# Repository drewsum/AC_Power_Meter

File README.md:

# AC_Power_Meter
ELEN3035 Final Project

AC Power Meter centered around an 8 bit PIC microcontroller

Built with KiCad 5.0.1 (with custom library), MPLAB X 5.05, and XC8 C compiler 1.45

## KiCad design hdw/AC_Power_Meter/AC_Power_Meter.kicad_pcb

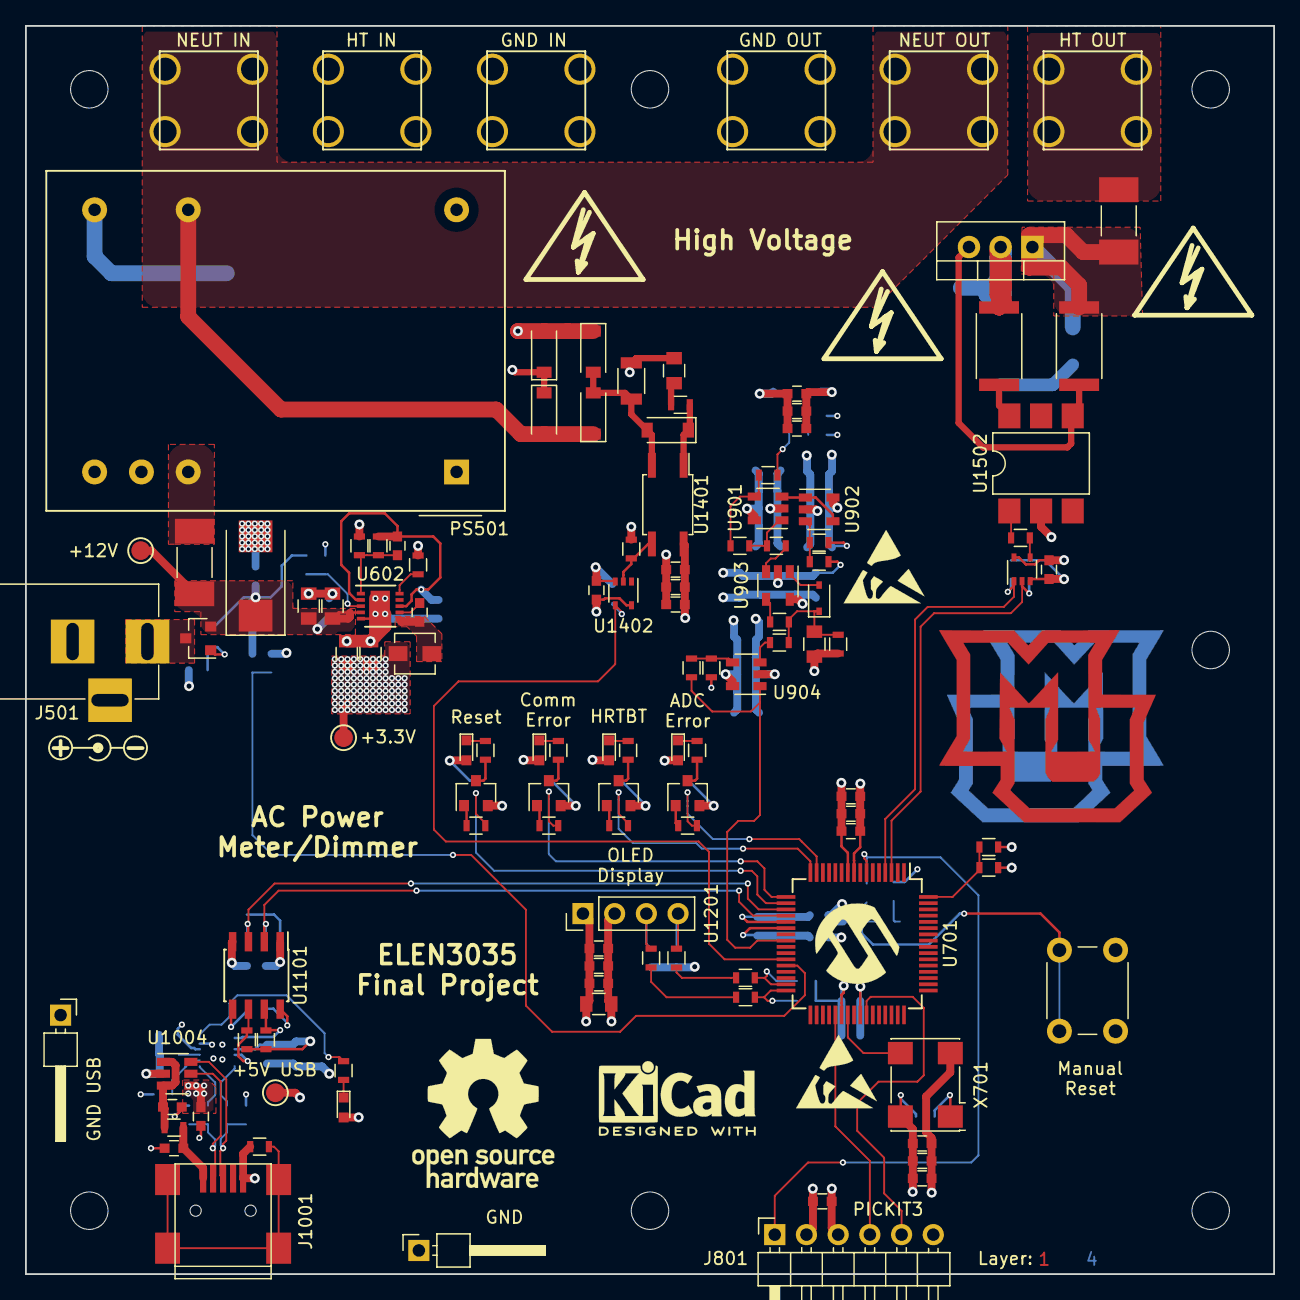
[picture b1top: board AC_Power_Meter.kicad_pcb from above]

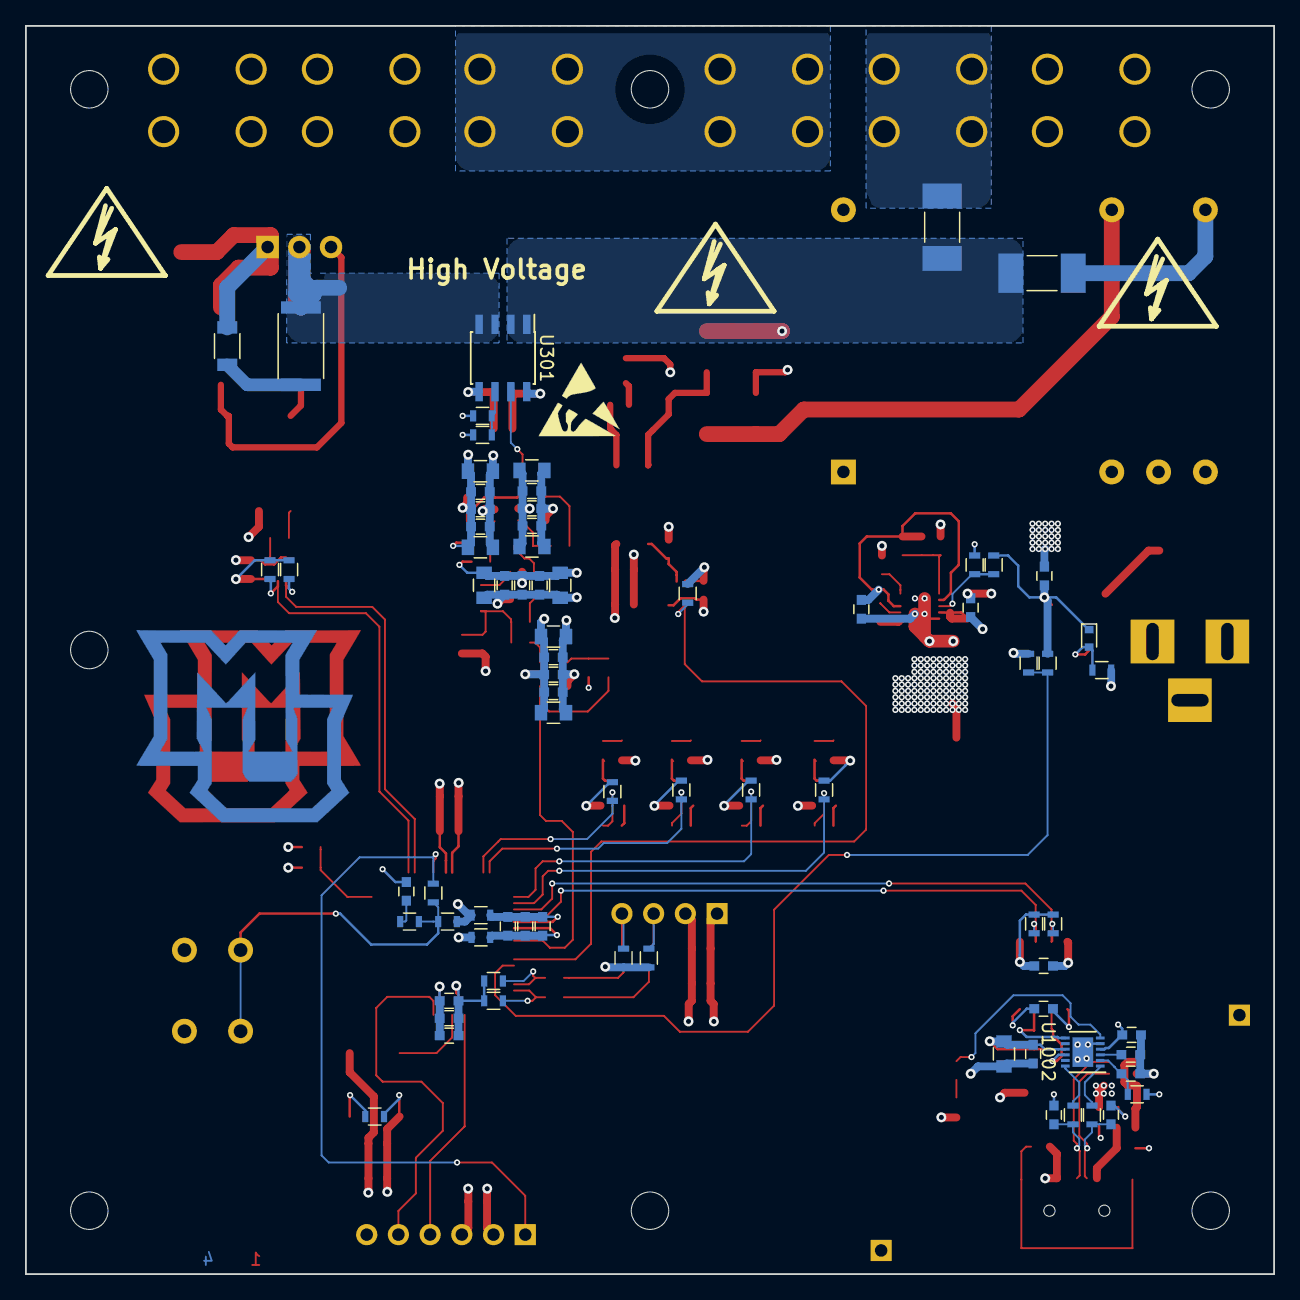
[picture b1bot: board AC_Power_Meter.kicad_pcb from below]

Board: 4 copper layers, 100.0 x 100.0 mm, 201 parts (75 on the bottom side), 95 nets.

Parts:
C301, C504, C604, C607, C701, C704, C708, C803, C807, C808, C901, C902, C911, C917, C1004, C1005, C1006, C1009, C1012, C1013, C1014, C1101, C1103, C1201, C1403, C1405, C1501: 0.1uF; C_0603
C302, C702, C705, C709, C804, C903, C904, C912, C918, C1202, C1404: 10nF; C_0603
C303, C703, C706, C710, C805, C905, C906, C913, C919, C1203, C1406: 1nF; C_0603
C505: 47uF; CP_Tantalum_Case-X_EIA-7343-43_Reflow
C601, C603, C1008: 4.7uF; C_0805
C605: 0.47uF; C_0603
C606: 15pF; C_0603
C608, C609, C907, C908, C914, C916, C920: 10uF; C_0805
C909, C910, C915, C921, C1204: 1uF; C_0805
C1010, C1011: 47pF; C_0603
C1401: 4.7nF; C_0805
C1502: 10nF; C_1206
D901: 1N4148WS; D_SOD-323
D1002: Yellow; LED_0603
D1401, D1402, D1403, D1404, D1405: BAV21; D_SOD-123
D1601, D1605: Red; LED_0603
D1602, D1604: Green; LED_0603
F201, F401: 15A; Fuse_CB61F
F501, F502: 3.15A; Fuse_CB61F
J201: HT_IN; Keystone_8191
J202: NEUT_IN; Keystone_8191
J203: EARTH_IN; Keystone_8191
J401: HT_OUT; Keystone_8191
J402: NEUT_OUT; Keystone_8191
J403: EARTH_OUT; Keystone_8191
J501: AUX_IN; BARREL_JACK
J801: Prog; PICKIT3_Header
J1001: USB_B_Mini; USB_Mini-B
L601: 3.3u; L_Vishay_IHLP-1212
L801, L802, L1001, L1002: 600R 0.5A; L_0603
MH1301, MH1302, MH1303, MH1305, MH1306, MH1307, MH1308: MountingHole; MountingHole_3mm
PS501: TMLM04112; ACDC-Conv_Traco-TMLM-04
Q501: DMP3099L-7; SOT-23
Q1401, Q1402, Q1403, Q1404: 2N7002; SOT-23
Q1501: BT139-600; TO-220-3_Vertical
R301, R501, R508, R602, R603, R606, R703, R704, R705, R805, R901, R902, R904, R905, R906, R909, R910, R1004, R1101, R1102, R1103, R1104, R1203, R1204, R1404, R1501, R1502, R1601, R1602, R1606, R1609: 10k; R_0603
R302, R701, R702, R806, R1201, R1202: 0; R_0603
R502, R903: 3.3k; R_0603
R605: 80.6k; R_0603
R607: 43.2k; R_0603
R608, R907: 1M; R_0603
R609: 576k; R_0603
R807, R908, R1009, R1402, R1603, R1604, R1608, R1611: 1k; R_0603
R1007, R1008: 27; R_0603
R1401: 100k; R_1206
R1403: 100k; R_0603
R1405, R1406, R1407, R1408: 10; R_0603
R1503: 220; R_0603
R1504: 1k; R_2512
R1505: 180; R_2512
R1506: 39; R_2512
SW801: MRESET; SW_PUSH_6mm
TP501, TP601, TP1001: TP; Measurement_Point_Round-SMD-Pad_Small
TP502, TP1002: TP; Pin_Header_Angled_1x01_Pitch2.54mm
U301: ACS722LLCTR-20AB; SOIC-8_3.9x4.9mm_Pitch1.27mm
U602: LT3973-DD; DFN-10-1EP_3x3mm_Pitch0.5mm
U701: PIC18LF67K40-I/PT; TQFP-64_10x10mm_Pitch0.5mm
U901, U902, U903, U904: LTC6240IS5; SOT-23-5
U1002: FT234XD; DFN-12-1EP_3x3mm_Pitch0.45mm
U1004: TPD3S014DBVR; SOT-23-6
U1101: ISO7321C; SOIC-8_3.9x4.9mm_Pitch1.27mm
U1201: SSD1306; Pin_Header_Straight_1x04_Pitch2.54mm
U1401: LTV-356T; SO-4_4.4x3.6mm_Pitch2.54mm
U1402: 74LVC1G17; SOT-353_SC-70-5
U1501: 74LVC1G32; SOT-353_SC-70-5
U1502: FOD4218; SMDIP-6_W7.62mm
X701: ASV-16.000MHz; Oscillator_SMD_Abracon_ASV-4pin_7.0x5.1mm
Z501: UDZSTE-175.1B; D_SOD-523

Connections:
+0.825V_REF: U901.3, U902.1, U902.4
+3.3VADC: C803.1, C804.1, C805.1, L801.2, U701.21
+3V3: C301.1, C302.1, C303.1, C606.1, C607.1, C608.1, C609.1, C701.1, C702.1, C703.1, C704.1, C705.1, C706.1, C708.1, C709.1, C710.1, C807.1, C901.1, C902.1, C903.1, C904.1, C905.1, C906.1, C907.1, C908.1, C909.1, C910.1, C911.1, C912.1, C913.1, C914.1, C915.1, C917.1, C918.1, C919.1, C920.1, C921.1, C1101.1, C1201.1, C1202.1, C1203.1, C1204.1, C1403.1, C1404.1, C1405.1, C1406.1, C1501.1, D1601.2, D1602.2, D1604.2, D1605.2, J801.2, L601.2, L801.1, R301.1, R602.1, R608.1, R703.1, R704.1, R705.1, R805.1, R902.1, R1101.2, R1102.2, R1203.1, R1204.1, R1601.1, TP601.1, U301.8, U602.2, U602.8, U701.10, U701.38, U901.5, U902.5, U903.5, U904.5, U1101.1, U1201.1, U1401.4, U1402.5, U1501.5, X701.4
+5V_USB: C1005.1, C1006.1, C1008.1, C1012.1, C1103.1, D1002.2, R1004.1, R1103.2, R1104.2, TP1001.1, U1002.4, U1002.9, U1004.4, U1101.8
+12V: C504.1, C505.1, C601.1, C603.1, C604.1, F502.1, Q501.2, R501.1, R605.1, TP501.1, U602.4, Z501.1
/USB UART Bridge/BRIDGE_USB+: R1007.1, U1002.12
/USB UART Bridge/BRIDGE_USB-: R1008.2, U1002.1
/USB UART Bridge/CONN_USB+: C1010.1, J1001.3, R1007.2, U1004.6
/USB UART Bridge/CONN_USB-: C1011.1, J1001.2, R1008.1, U1004.5
ADC_Error: R1408.2, R1609.1, U701.15
CLKIN: U701.39, X701.3
Comm_Error: R1406.2, R1602.1, U701.17
Earth_Protective: J203.1, J403.1
GND: C301.2, C302.2, C303.2, C504.2, C505.2, C601.2, C603.2, C604.2, C607.2, C608.2, C609.2, C701.2, C702.2, C703.2, C704.2, C705.2, C706.2, C708.2, C709.2, C710.2, C807.2, C808.2, C901.2, C902.2, C903.2, C904.2, C905.2, C906.2, C907.2, C908.2, C909.2, C910.2, C911.2, C912.2, C913.2, C914.2, C915.2, C916.2, C917.2, C918.2, C919.2, C920.2, C921.2, C1101.2, C1201.2, C1202.2, C1203.2, C1204.2, C1403.2, C1404.2, C1405.2, C1406.2, C1501.2, J501.2, J501.3, J801.3, L802.2, PS501.3, Q1401.2, Q1402.2, Q1403.2, Q1404.2, R302.1, R502.2, R508.2, R603.2, R606.2, R607.2, R609.2, R903.2, R907.2, R909.2, R1403.2, R1404.2, R1501.2, R1502.2, R1602.2, R1606.2, R1609.2, SW801.1, TP502.1, U301.5, U602.5, U602.11, U701.9, U701.41, U901.2, U902.2, U903.2, U904.2, U1101.4, U1201.2, U1402.3, U1501.3, U1502.2, X701.2
GNDA: C803.2, C804.2, C805.2, L802.1, U701.22
GNDPWR: D1402.2, D1404.2, D1405.2, R1401.2, U1401.2
GND_USB: C1004.2, C1005.2, C1006.2, C1008.2, C1009.2, C1010.2, C1011.2, C1012.2, C1013.2, C1014.2, C1103.2, J1001.5, L1002.2, TP1002.1, U1002.5, U1002.13, U1004.2, U1101.5
HT: D1401.2, D1402.1, F201.1, F501.2, U301.1, U301.2
Heartbeat: R1407.2, R1606.1, U701.16
I2C_SCL: R702.2, R1202.2
I2C_SDA: R701.1, R1201.1
ICSPCLK: J801.5, U701.42
ICSPDAT: J801.4, U701.37
ISNS_ADC: R910.2, U701.24, U904.1
ISNS_HT_OUT: Q1501.2, R1505.2, R1506.1, U301.3, U301.4
ISNS_OUT: R901.2, U301.7
NEUT: D1403.2, D1404.1, J202.1, J402.1, PS501.6
unnamed: C605.1, U602.7
unnamed: C605.2, L601.1, U602.6
unnamed: C606.2, R608.2, R609.1, U602.1
unnamed: C808.1, R806.1
unnamed: C916.1, D901.1, R906.2, R907.1, R908.1
unnamed: C1004.1, R1004.2, U1002.2
unnamed: C1009.1, U1002.3
unnamed: C1013.1, L1001.2, U1004.1, U1004.3
unnamed: C1014.1, J1001.1, L1001.1
unnamed: C1401.1, R1402.1
unnamed: C1401.2, D1401.1, D1403.1, R1401.1
unnamed: C1502.1, R1506.2
unnamed: D901.2, U903.1
unnamed: D1002.1, R1009.1
unnamed: D1405.1, R1402.2, U1401.1
unnamed: D1601.1, R1603.1
unnamed: D1602.1, R1604.1
unnamed: D1604.1, R1608.1
unnamed: D1605.1, R1611.1
unnamed: F201.2, J201.1
unnamed: F401.1, J401.1
unnamed: F501.1, PS501.5
unnamed: F502.2, PS501.2
unnamed: J501.1, Q501.3
unnamed: J1001.6, L1002.1
unnamed: Q501.1, R508.1, Z501.2
unnamed: Q1401.1, R1405.1
unnamed: Q1401.3, R1603.2
unnamed: Q1402.1, R1406.1
unnamed: Q1402.3, R1604.2
unnamed: Q1403.1, R1407.1
unnamed: Q1403.3, R1608.2
unnamed: Q1404.1, R1408.1
unnamed: Q1404.3, R1611.2
unnamed: Q1501.3, R1504.1, U1502.4
unnamed: R301.2, R302.2, U301.6
unnamed: R605.2, R606.1, U602.3
unnamed: R607.1, U602.10
unnamed: R701.2, R704.2, U701.31
unnamed: R702.1, R703.2, U701.32
unnamed: R705.2, X701.1
unnamed: R901.1, R904.1, U901.4
unnamed: R902.2, R903.1, U902.3
unnamed: R904.2, R905.1, U901.1
unnamed: R905.2, U903.3
unnamed: R906.1, U903.4
unnamed: R908.2, U904.3
unnamed: R909.1, R910.1, U904.4
unnamed: R1201.2, R1204.2, U1201.4
unnamed: R1202.1, R1203.2, U1201.3
unnamed: R1403.1, U1401.3, U1402.2
unnamed: R1503.1, U1502.1
unnamed: R1503.2, U1501.4
unnamed: R1505.1, U1502.6
POS3P3_ADC: R602.2, R603.1, U701.64
POS12_ADC: R501.2, R502.1, U701.28
SSR_Dim: R1501.1, U701.4, U1501.1
SSR_Force: R1502.1, U701.3, U1501.2
TRIAC_HT_OUT: C1502.2, F401.2, Q1501.1, R1504.2
USB_UART_RX: R1101.1, U701.20, U1101.2
USB_UART_RX_ISO: R1104.1, U1002.7, U1101.7
USB_UART_TX: R1102.1, U701.19, U1101.3
USB_UART_TX_ISO: R1103.1, U1002.10, U1101.6
Zero_Cross_Detect: R1404.1, U701.27, U1402.4
~Active: R1405.2, R1601.2, U701.18
~MCLR: J801.1, R807.1, U701.7
~MRST: R805.2, R806.2, R807.2, SW801.2
~USB_ACTIVE: R1009.2, U1002.6

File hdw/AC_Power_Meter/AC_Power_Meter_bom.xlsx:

References | Value | Quantity Per PCB | Digi-Key PN | Footprint | Dielectric | Voltage | Tolerance | Ampacity | Wattage | Config
C301 C504 C604 C607 C701 C704 C708 C803 C807 C808 C901 C902 C911 C917 C1004 C10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 | 0.1uF | 27 | 490-8020-1-ND | 603 | X7R | 50V
C605 | 0.47uF | 1 | 490-3291-1-ND | 603 | X7R | 25V
C302 C702 C705 C709 C804 C903 C904 C912 C918 C1202 C1404 | 10nF | 11 | 1276-1921-1-ND | 603 | X7R | 50V
C1502 | 10nF | 1 | 445-2291-1-ND | 1206 | X7R | 630V
C608 C609 C907 C908 C914 C916 C920 | 10uF | 7 | 490-10517-1-ND | 805 | X7R | 6.3V
C606 | 15pF | 1 | 478-10290-1-ND | 603 | C0G/NP0 | 50V
C303 C703 C706 C710 C805 C905 C906 C913 C919 C1203 C1406 | 1nF | 11 | 478-1215-1-ND | 603 | X7R | 50V
C909 C910 C915 C921 C1204 | 1uF | 5 | 490-1695-1-ND | 805 | X7R | 10V
C1401 | 4.7nF | 1 | 399-9245-1-ND | 805 | X7R | 200V
C601 C603 C1008 | 4.7uF | 3 | 478-10056-1-ND | 805 | X7R | 25V
C1010 C1011 | 47pF | 2 | 478-1171-1-ND | 603 | C0G/NP0 | 50V
C505 | 47uF | 1 | 478-3938-1-ND | 7343 |  | 16V | 0.1
D901 | 1N4148WS | 1 | 1N4148WSFSCT-ND
D1401 D1402 D1403 D1404 D1405 | BAV21 | 5 | BAV21W-FDICT-ND
D1602 D1604 | Green | 2 | 160-1446-1-ND | 603
D1601 D1605 | Red | 2 | 160-1447-1-ND | 603
D1002 | Yellow | 1 | 160-1448-1-ND | 603
F201 F401 | 15A | 2 | 283-4372-1-ND
F501 F502 | 3.15A | 2 | 283-4107-1-ND
HS1501 | Heatsink | 1
J501 | AUX_IN | 1
J203 | EARTH_IN | 1 | 36-8191-ND
J403 | EARTH_OUT | 1 | 36-8191-ND
J201 | HT_IN | 1 | 36-8191-ND
J401 | HT_OUT | 1 | 36-8191-ND
J202 | NEUT_IN | 1 | 36-8191-ND
J402 | NEUT_OUT | 1 | 36-8191-ND
J404 | Output Socket | 1 | Q337-ND
J801 | Prog | 1
J1001 | USB_B_Mini | 1 | 732-2109-1-ND
L601 | 3.3u | 1 | 541-2567-1-ND | IHLP1212 |  |  | 0.2 | 2.7A
L801 L802 L1001 L1002 | 600R 0.5A | 4 | 732-1593-1-ND
MK201 MK203 MK1303 MK1304 MK1307 MK1311 MK1312 MK1315 MK1316 | 4-40 Screw | 9 | 36-9502-ND 36-9900-ND
MK1305 MK1306 MK1309 MK1313 MK1314 MK1317 MK1318 | 4-40 Standoff | 7 | 36-8400-ND
MK1301 | Housing | 1
MK1302 | Lid | 1
MK202 MK204 | Nut | 2 | 36-4694-ND
P201 | AC In Socket | 1 | Q223-ND
PS501 | TMLM04112 | 1 | 1951-1352-ND
Q1401 Q1402 Q1403 Q1404 | 2N7002 | 4
Q1501 | BT139-600 | 1 | 1740-1050-ND
Q501 | DMP3099L-7 | 1 | DMP3099L-7DICT-ND
R701 R702 R1201 R1202 | 0 | 4 | P0.0GCT-ND | 603 |  |  | 0.01 |  | 1/10W
R302 R806 | 0 | 0 |  | 603 |  |  | 0.01 |  | 1/10W | None
R1405 R1406 R1407 R1408 | 10 | 4 | MCT0603-10.0-CFCT-ND | 603 |  |  | 0.01 |  | 43110
R1401 | 100k | 1 | RHM100KICT-ND | 1206 |  |  | 0.05 |  | 1/2W
R1403 | 100k | 1 | P100KHCT-ND | 603 |  |  | 0.01 |  | 1/10W
R301 R501 R508 R602 R603 R606 R703 R704 R705 R805 R901 R902 R904 R905 R906 R909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 | 10k | 31 | RHM10KADCT-ND | 603 |  |  | 0.01 |  | 1/10W
R1505 | 180 | 1 | A115990CT-ND | 2512 |  |  | 0.01 |  | 1W
R608 R907 | 1M | 2 | A130109CT-ND | 603 |  |  | 0.01 |  | 1/10W
R807 R908 R1009 R1402 R1603 R1604 R1608 R1611 | 1k | 8 | MCT0603-1.00K-CFCT-ND | 603 |  |  | 0.01 |  | 1/10W
R1504 | 1k | 1 | 541-1.0KXCT-ND | 2512 |  |  | 0.05 |  | 1W
R1503 | 220 | 1 | 311-220HRCT-ND | 603 |  |  | 0.01 |  | 1/10W
R1007 R1008 | 27 | 2 | P27.0HCT-ND | 603 |  |  | 0.01 |  | 1/10W
R502 R903 | 3.3k | 2 | 311-3.30KHRCT-ND | 603 |  |  | 0.01 |  | 1/10W
R1506 | 39 | 1 | 541-39XCT-ND | 2512 |  |  | 0.05 |  | 1W
R607 | 43.2k | 1 | P43.2KHCT-ND | 603 |  |  | 0.01 |  | 1/10W
R609 | 576k | 1 | 311-576KHRCT-ND | 603 |  |  | 0.01 |  | 1/10W
R605 | 80.6k | 1 | P80.6KHCT-ND | 603 |  |  | 0.01 |  | 1/10W
SW801 | MRESET | 1
U1402 | 74LVC1G17 | 1 | 296-11934-1-ND
U1501 | 74LVC1G32 | 1 | 296-9848-1-ND
U301 | ACS722LLCTR-20AB | 1 | 620-1637-1-ND
U1502 | FOD4218 | 1 | FOD4218S-ND
U1002 | FT234XD | 1 | 768-1178-1-ND
U1101 | ISO7321C | 1 | 296-42102-1-ND
U602 | LT3973-DD | 1 | LT3973EDD#PBF-ND
U901 U902 U903 U904 | LTC6240IS5 | 4 | LTC6240IS5#TRMPBFCT-ND
U1401 | LTV-356T | 1 | 160-1337-1-ND
U701 | PIC18LF67K40-I/PT | 1 | PIC18LF67K40-I/PT-ND
U1201 | SSD1306 | 1
U1004 | TPD3S014DBVR | 1 | 296-38835-1-ND
X701 | ASV-16.000MHz | 1 | 535-10072-1-ND
Z501 | UDZSTE-175.1B | 1 | UDZSTE-175.1BCT-ND | SOD323 |  | 5.1V

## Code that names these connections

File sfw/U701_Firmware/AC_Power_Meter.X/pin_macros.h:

/* Microchip Technology Inc. and its subsidiaries.  You may use this software 
 * and any derivatives exclusively with Microchip products. 
 * 
 * THIS SOFTWARE IS SUPPLIED BY MICROCHIP "AS IS".  NO WARRANTIES, WHETHER 
 * EXPRESS, IMPLIED OR STATUTORY, APPLY TO THIS SOFTWARE, INCLUDING ANY IMPLIED 
 * WARRANTIES OF NON-INFRINGEMENT, MERCHANTABILITY, AND FITNESS FOR A 
 * PARTICULAR PURPOSE, OR ITS INTERACTION WITH MICROCHIP PRODUCTS, COMBINATION 
 * WITH ANY OTHER PRODUCTS, OR USE IN ANY APPLICATION. 
 *
 * IN NO EVENT WILL MICROCHIP BE LIABLE FOR ANY INDIRECT, SPECIAL, PUNITIVE, 
 * INCIDENTAL OR CONSEQUENTIAL LOSS, DAMAGE, COST OR EXPENSE OF ANY KIND 
 * WHATSOEVER RELATED TO THE SOFTWARE, HOWEVER CAUSED, EVEN IF MICROCHIP HAS 
 * BEEN ADVISED OF THE POSSIBILITY OR THE DAMAGES ARE FORESEEABLE.  TO THE 
 * FULLEST EXTENT ALLOWED BY LAW, MICROCHIP'S TOTAL LIABILITY ON ALL CLAIMS 
 * IN ANY WAY RELATED TO THIS SOFTWARE WILL NOT EXCEED THE AMOUNT OF FEES, IF 
 * ANY, THAT YOU HAVE PAID DIRECTLY TO MICROCHIP FOR THIS SOFTWARE.
 *
 * MICROCHIP PROVIDES THIS SOFTWARE CONDITIONALLY UPON YOUR ACCEPTANCE OF THESE 
 * TERMS. 
 */

/* 
 * File:   
 * Author: 
 * Comments:
 * Revision history: 
 */

// This is a guard condition so that contents of this file are not included
// more than once.  
#ifndef PIN_MACROS_H
#define	PIN_MACROS_H

#include <xc.h> // include processor files - each processor file is guarded.  


// Port F
#define nACTIVE_PIN     LATFbits.LATF0
#define HEARTBEAT_PIN   LATFbits.LATF2
#define COMM_ERROR_PIN  LATFbits.LATF1
#define ADC_ERROR_PIN   LATFbits.LATF3

// Port G
#define SSR_FORCE_PIN   LATGbits.LATG0
#define SSR_DIM_PIN     LATGbits.LATG1



#endif	/* PIN_MACROS_H */

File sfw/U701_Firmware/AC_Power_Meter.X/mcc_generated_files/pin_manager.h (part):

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// get/set ISNS_ADC aliases
#define ISNS_ADC_TRIS                 TRISAbits.TRISA0
#define ISNS_ADC_LAT                  LATAbits.LATA0
#define ISNS_ADC_PORT                 PORTAbits.RA0
#define ISNS_ADC_WPU                  WPUAbits.WPUA0
#define ISNS_ADC_OD                   ODCONAbits.ODCA0
#define ISNS_ADC_ANS                  ANSELAbits.ANSELA0
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// get/set POS12_ADC aliases
#define POS12_ADC_TRIS                 TRISAbits.TRISA4
#define POS12_ADC_LAT                  LATAbits.LATA4
#define POS12_ADC_PORT                 PORTAbits.RA4
#define POS12_ADC_WPU                  WPUAbits.WPUA4
#define POS12_ADC_OD                   ODCONAbits.ODCA4
#define POS12_ADC_ANS                  ANSELAbits.ANSELA4
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// get/set POS3P3_ADC aliases
#define POS3P3_ADC_TRIS                 TRISEbits.TRISE2
#define POS3P3_ADC_LAT                  LATEbits.LATE2
#define POS3P3_ADC_PORT                 PORTEbits.RE2
#define POS3P3_ADC_WPU                  WPUEbits.WPUE2
#define POS3P3_ADC_OD                   ODCONEbits.ODCE2
#define POS3P3_ADC_ANS                  ANSELEbits.ANSELE2
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
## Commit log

2018-10-01 Added KiCad project with a few sheets filled out
2018-10-01 Populated USB circuit pages
2018-10-01 Added PDF
2018-10-02 Added zero cross detect circuit
2018-10-02 Added TRIAC circuit and POS12 AC/DC converter
2018-10-02 Added AC input and output connections, added mechanical components
2018-10-02 Added supporting parts for OLED display
2018-10-03 Added +3.3V power supply, +12V window comparator, a few design files
2018-10-03 Added MU logo and titles to all sheets
2018-10-03 Updated MU logo to crisper image
2018-10-04 Added ORing circuit to TRIAC page
2018-10-04 Added series resistor in ZCD circuit
2018-10-05 Revised signal conditioning, cleaned up a lot of pages
2018-10-05 Added pushbuttons sheet, prelim wiring on micro
2018-10-05 Rewired a few micro symbols, add FMW notes
2018-10-05 Updated PDF
2018-10-05 Updated most footprints
2018-10-06 Finished assigning footprints, added netlist
2018-10-06 Pulled parts into PCB
2018-10-06 Arranged a few pages of components
2018-10-07 Nailed down board outline, placed a few sections
2018-10-07 Placed a lot more parts, netlist cleanup
2018-10-07 Finished placing parts
2018-10-07 Made a fw minor adjustments to PCB
2018-10-07 Added some PCB design rules
2018-10-07 Finished assigning design rules to nets
2018-10-07 Routed much more of the board, design rule fixes
2018-10-08 MOAR ROUTING
2018-10-08 Finished routing, adding bells and whistles
2018-10-08 Added a few more finishing touches, moved some components
2018-10-09 A few routing adjustments and more graphics added to PCB
2018-10-09 Serious BOM scrubbing to drive price down
2018-10-10 Finished up PCB
2018-10-27 Modified schematic and board files slightly
2018-10-27 Started writing PIC firmware
2018-10-28 Added ADC and timer functionality to measure supply rails and print to terminal
2018-10-28 Added more cool functionality
2018-11-01 Added a lot of functionality in formware
2018-11-02 Cleaned up set dimming percentage command
2018-11-02 Added functionality to set rms values to 0.0 when SSR is off
2018-11-02 Cleaned up help message
2018-11-02 Cleaned up some variables, added load on time measurement
2018-11-03 Added serial support for printing device ID
2018-11-04 Added ADC error detection and relevant serial commands
2018-11-04 Added VCC overvoltage detection and related serial commands
2018-11-05 Heavily revised cause of reset functionality
2018-11-05 Fixed issues with VCC overvoltage detection
2018-11-06 Removed overkill newlines in serial interface replies
2018-11-06 Further cleaned up serial LUT code
2018-11-06 Got ADC digital filtering working
2018-11-06 Added output state check commands
2018-11-06 Cleaned up more serial commands
2018-11-06 Added functionality to save and retrieve maximum RMS current and power
2018-11-06 Added clear max values command
2018-11-07 Added more maximum value functionality
2018-11-07 cleaned up erase max values functionality, help serial commands
2018-11-07 Updated README to include software versions
2018-11-08 Added dimming functionality
2018-11-08 Added HLVD detect functionality to save total energy to EEPROM at power fail
2018-11-08 Added energy EEPROM periodic write interupt routines
2018-11-09 broken ADC
2018-11-09 ADC and Temp Sensor bug fixes
2018-11-13 Added baseline OLED I2C driver
2018-11-13 Added expanded error handling
2018-11-13 Added more elegant OLED ram buffer update method
2018-11-13 Resolved some comm error detection issues
2018-11-13 Added a lot of OLED support
2018-11-16 Fixed bug with upper case S in OLED font array
2018-11-17 Fixed bug where pickit3 would write over saved EEPROM variables, other bug fixes
2018-11-17 fixed uart comm error LED bug
2018-11-17 More OLED bug fixes, variable frame periods
2018-11-18 Added awesome terminal boot message
2018-11-18 Added unsupported command response
2018-11-18 Bug fixes
2018-11-18 Added device and measurement summary serial commands
2018-11-18 Added live update test code
2018-11-19 Schematic cleanup, live updates working in code
2018-11-19 Current sense ADC bug fixes
2018-12-04 Fixed ISNS DC offset issue

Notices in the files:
sfw/U701_Firmware/AC_Power_Meter.X/mcc_generated_files/pin_manager.h:
(c) 2018 Microchip Technology Inc. and its subsidiaries.
